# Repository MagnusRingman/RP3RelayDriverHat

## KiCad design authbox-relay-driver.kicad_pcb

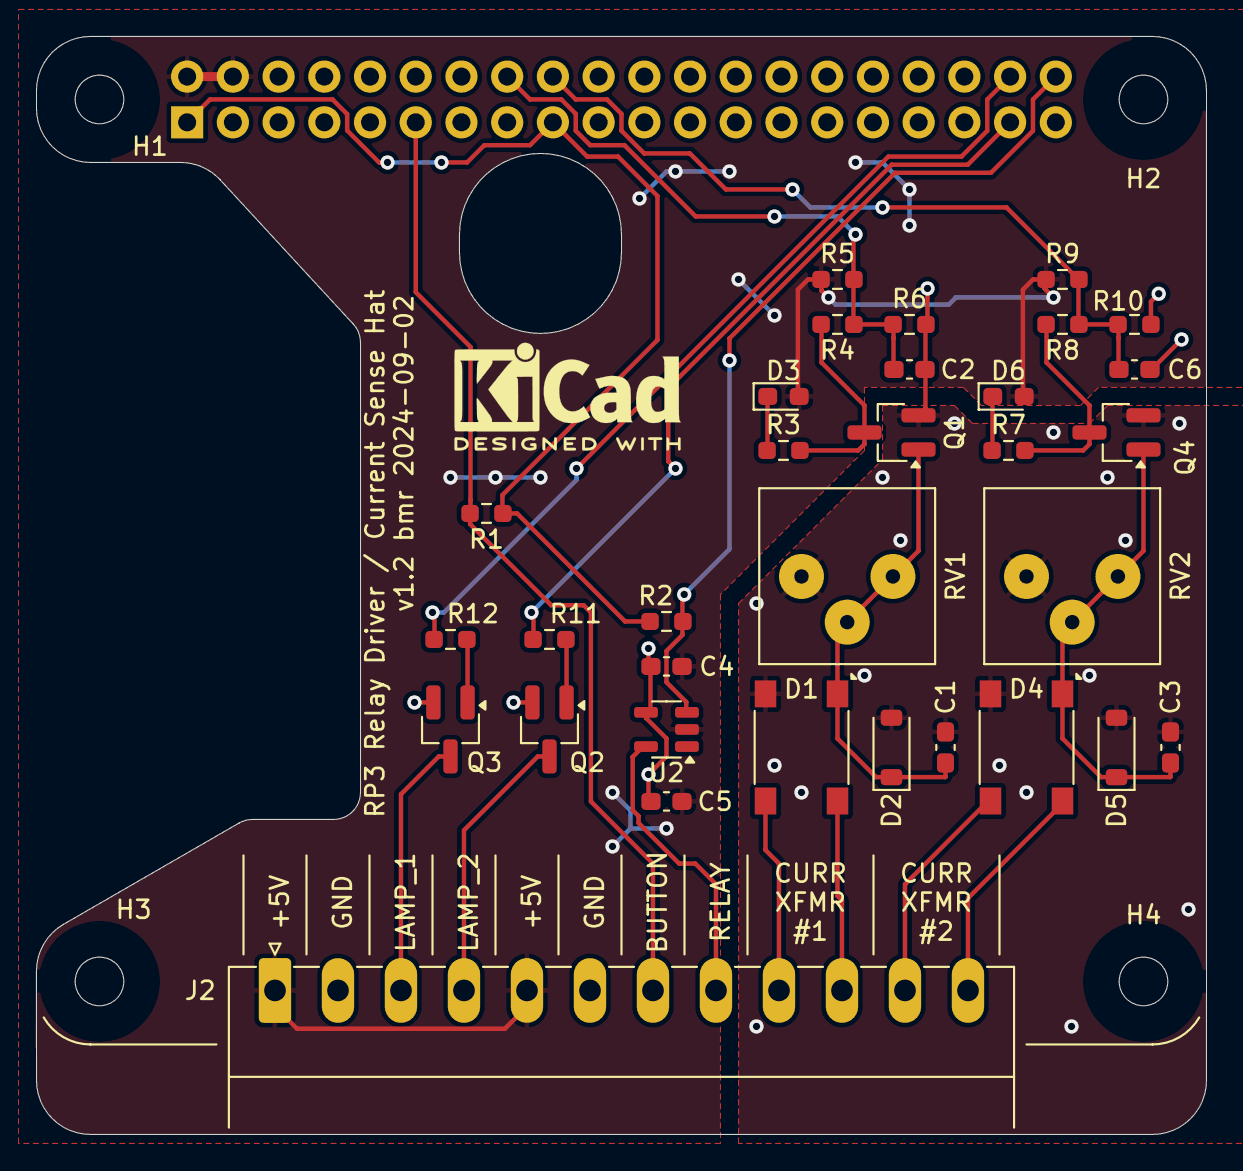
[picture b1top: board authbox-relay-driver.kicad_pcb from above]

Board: 2 copper layers, 65.0 x 61.0 mm, 37 parts (1 on the bottom side), 24 nets.

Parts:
C1, C3: 1µF; C_0603_1608Metric_Pad1.08x0.95mm_HandSolder
C2, C6: 10µF; C_0603_1608Metric_Pad1.08x0.95mm_HandSolder
C4, C5: 100nF; C_0603_1608Metric_Pad1.08x0.95mm_HandSolder
D1, D4: MDB10S; Diode_Bridge_Diotec_ABS
D2, D5: MMSZ12T; D_SOD-123
D3, D6: LED; LED_0603_1608Metric_Pad1.05x0.95mm_HandSolder
H1, H2, H3, H4: MountingHole; MountingHole_2.7mm
J1: GPIO; PinSocket_2x20_P2.54mm_Vertical
J2: Screw_Terminal_01x12; PhoenixContact_MC_1,5_12-G-3.5_1x12_P3.50mm_Horizontal
Q1, Q4: 2N7002L; SOT-23_Handsoldering
Q2, Q3: BC846; SOT-23_Handsoldering
R1, R2, R5, R9: 4k7; R_0603_1608Metric_Pad0.98x0.95mm_HandSolder
R3, R7: 1k; R_0603_1608Metric_Pad0.98x0.95mm_HandSolder
R4, R8: 100; R_0603_1608Metric_Pad0.98x0.95mm_HandSolder
R6, R10: 10k; R_0603_1608Metric_Pad0.98x0.95mm_HandSolder
R11, R12: 3k3; R_0603_1608Metric_Pad0.98x0.95mm_HandSolder
RV1, RV2: 5M; Potentiometer_Bourns_3386P_Vertical
U2: MCP1415; SOT-23-5

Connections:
+3V3: J1.1, J1.17, R1.1, R2.1
+5V: C4.1, C5.1, D3.2 (A), D6.2 (A), J1.2, J1.4, J2.1, J2.5, R5.1, R9.1, U2.2 (Vdd)
/current-sense/CURR_A: D1.3, J2.9
/current-sense/CURR_B: D1.4, J2.10
/sheet5C9BD5B1/CURR_A: D4.3, J2.11
/sheet5C9BD5B1/CURR_B: D4.4, J2.12
B1_LOGIC: J1.11, J2.7, R1.2
CURRENT1: C2.1, J1.16, R4.1, R5.2, R6.1
CURRENT2: C6.1, J1.18, R8.1, R9.2, R10.1
GND: C1.2, C2.2, C3.2, C4.2, C5.2, C6.2, D1.2 (-), D2.2 (A), D4.2 (-), D5.2 (A), J1.6, J1.9, J1.14, J1.20, J1.25, J1.30, J1.34, J1.39, J2.2, J2.6, Q1.2 (S), Q2.2 (E), Q3.2 (E), Q4.2 (S), R6.2, R10.2, RV1.1, RV2.1, U2.4 (GND)
HC_LOGIC: J1.40, R2.2, U2.3 (IN)
L1_LOGIC: J1.38, R12.1
L2_LOGIC: J1.37, R11.1
LAMP1: J2.3, Q3.3 (C)
LAMP2: J2.4, Q2.3 (C)
unnamed: C1.1, D1.1 (+), D2.1 (K), Q1.1 (G), RV1.2, RV1.3
unnamed: D3.1 (K), R3.1
unnamed: C3.1, D4.1 (+), D5.1 (K), Q4.1 (G), RV2.2, RV2.3
unnamed: D6.1 (K), R7.1
unnamed: J2.8, U2.5 (~OUT)
unnamed: Q1.3 (D), R3.2, R4.2
unnamed: Q2.1 (B), R11.2
unnamed: Q3.1 (B), R12.2
unnamed: Q4.3 (D), R7.2, R8.2

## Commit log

2019-01-19 Initial prototype. Has bugs.
2019-01-19 Fixed: * Rectifier bridge footprint. * Pad size for trimmer potentiometers.
2019-01-19 Re-generated plots after fixes in previous commit.
2019-04-06 Fixed a few solderability issues. Corrected the footprint for the rectifier bridges (D1 and D4).
2024-02-18 Replace out of stock 2V7002 with 2N7002. Upgrade to KiCad 7.0.
2024-09-17 Miscellaneous fixes: * Change to KiCad 8.0. * Modify the cutouts on the board to accomodate a different layout of the PoE hat (which sits below.) * Transfer the customized footprints into a project-s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
